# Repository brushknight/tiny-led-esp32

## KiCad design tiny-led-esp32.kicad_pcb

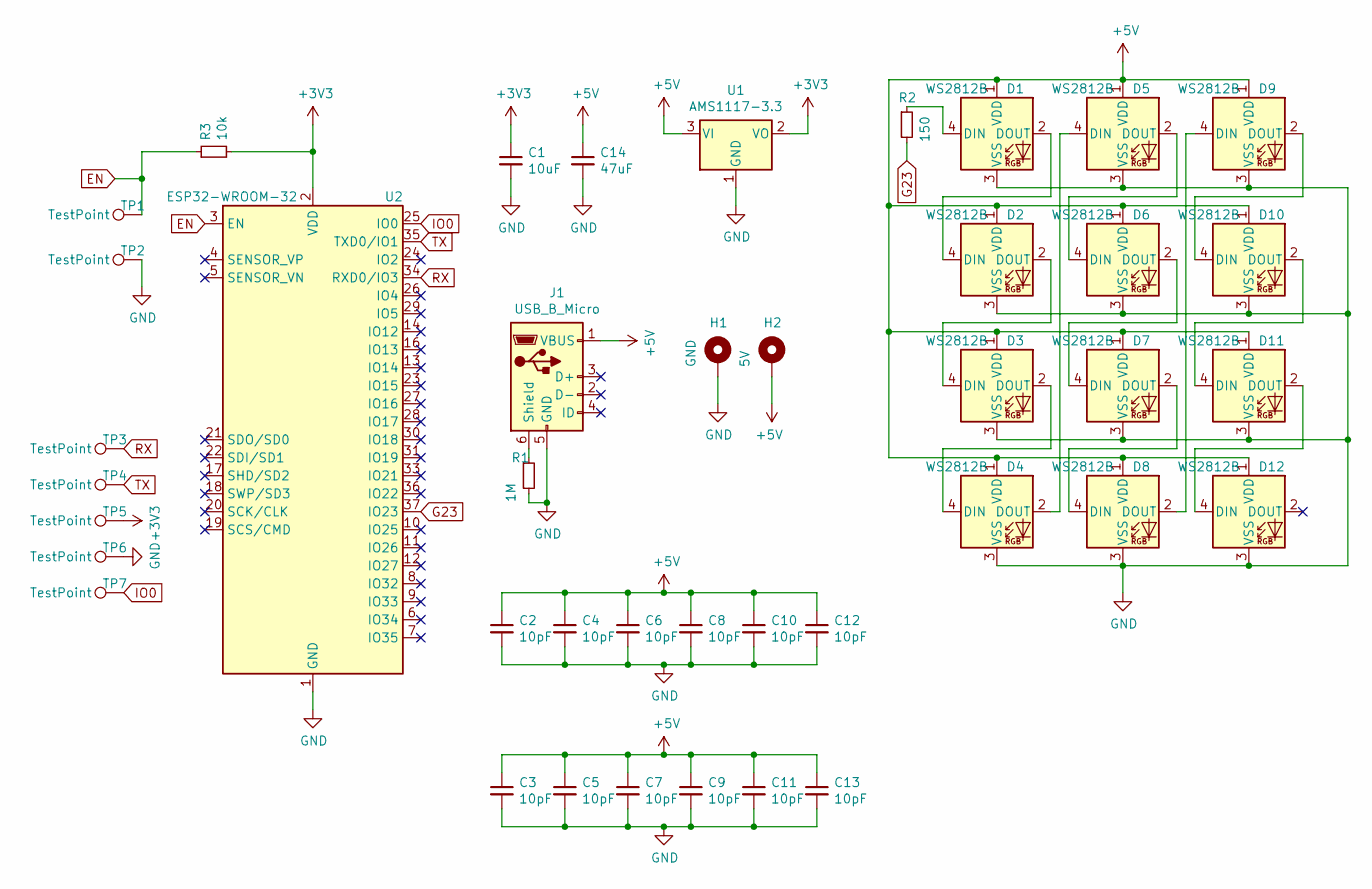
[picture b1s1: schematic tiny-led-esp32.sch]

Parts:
C1: 10uF; C_1206_3216Metric
C2, C3, C4, C5, C6, C7, C8, C9, C10, C11, C12, C13: 10pF; C_1206_3216Metric
C14: 47uF; C_1206_3216Metric
D1, D2, D3, D4, D5, D6, D7, D8, D9, D10, D11, D12: WS2812B; LED_WS2812B_PLCC4_5.0x5.0mm_P3.2mm
H1: GND; MountingHole_3.2mm_M3_Pad_Via
H2: 5V; MountingHole_3.2mm_M3_Pad_Via
J1: USB_B_Micro; USB_Micro-B_Wuerth_629105150521
R1: 1M; R_1206_3216Metric
R2: 150; R_1206_3216Metric
R3: 10k; R_1206_3216Metric
TP1, TP2, TP3, TP4, TP5, TP6, TP7: TestPoint; TestPoint_Pad_D2.5mm
U1: AMS1117-3.3; SOT-223-3_TabPin2
U2: ESP32-WROOM-32

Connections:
+3V3: C1.1, R3.2, TP5.1, U1.2 (VO), U2.2 (VDD)
+5V: C2.1, C3.1, C4.1, C5.1, C6.1, C7.1, C8.1, C9.1, C10.1, C11.1, C12.1, C13.1, C14.1, D1.1 (VDD), D2.1 (VDD), D3.1 (VDD), D4.1 (VDD), D5.1 (VDD), D6.1 (VDD), D7.1 (VDD), D8.1 (VDD), D9.1 (VDD), D10.1 (VDD), D11.1 (VDD), D12.1 (VDD), H2.1, J1.1 (VBUS), U1.3 (VI)
EN: R3.1, TP1.1, U2.3 (EN)
G23: R2.2, U2.37 (IO23)
GND: C1.2, C2.2, C3.2, C4.2, C5.2, C6.2, C7.2, C8.2, C9.2, C10.2, C11.2, C12.2, C13.2, C14.2, D1.3 (VSS), D2.3 (VSS), D3.3 (VSS), D4.3 (VSS), D5.3 (VSS), D6.3 (VSS), D7.3 (VSS), D8.3 (VSS), D9.3 (VSS), D10.3 (VSS), D11.3 (VSS), D12.3 (VSS), H1.1, J1.5 (GND), R1.2, TP2.1, TP6.1, U1.1 (GND), U2.1 (GND), U2.15 (GND), U2.38 (GND), U2.39 (GND)
IO0: TP7.1, U2.25 (IO0)
unnamed: D1.2 (DOUT), D2.4 (DIN)
unnamed: D1.4 (DIN), R2.1
unnamed: D2.2 (DOUT), D3.4 (DIN)
unnamed: D3.2 (DOUT), D4.4 (DIN)
unnamed: D4.2 (DOUT), D5.4 (DIN)
unnamed: D5.2 (DOUT), D6.4 (DIN)
unnamed: D6.2 (DOUT), D7.4 (DIN)
unnamed: D7.2 (DOUT), D8.4 (DIN)
unnamed: D8.2 (DOUT), D9.4 (DIN)
unnamed: D10.2 (DOUT), D11.4 (DIN)
unnamed: D9.2 (DOUT), D10.4 (DIN)
unnamed: D11.2 (DOUT), D12.4 (DIN)
unnamed: J1.6 (Shield), R1.1
RX: TP3.1, U2.34 (RXD0/IO3)
TX: TP4.1, U2.35 (TXD0/IO1)

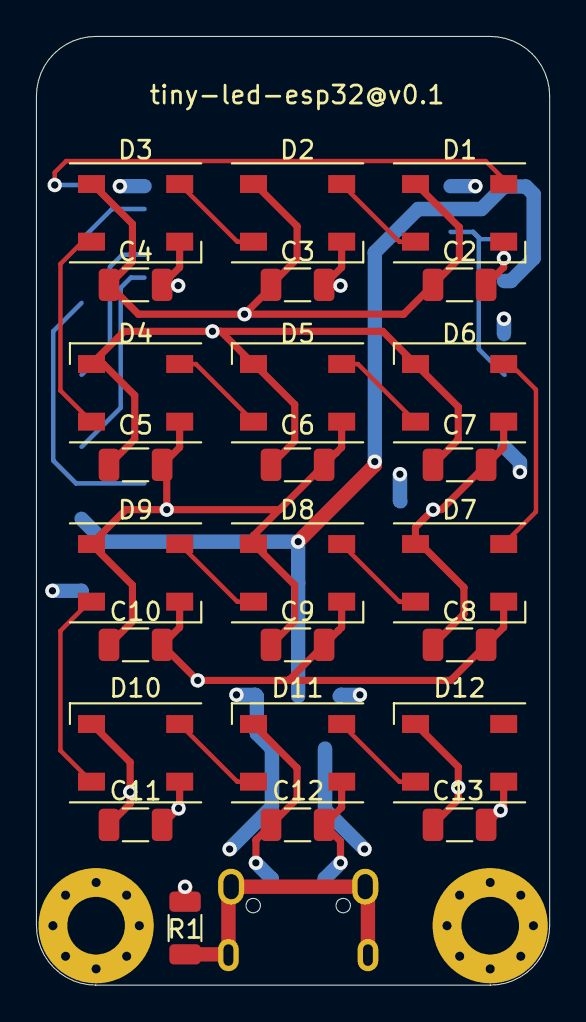
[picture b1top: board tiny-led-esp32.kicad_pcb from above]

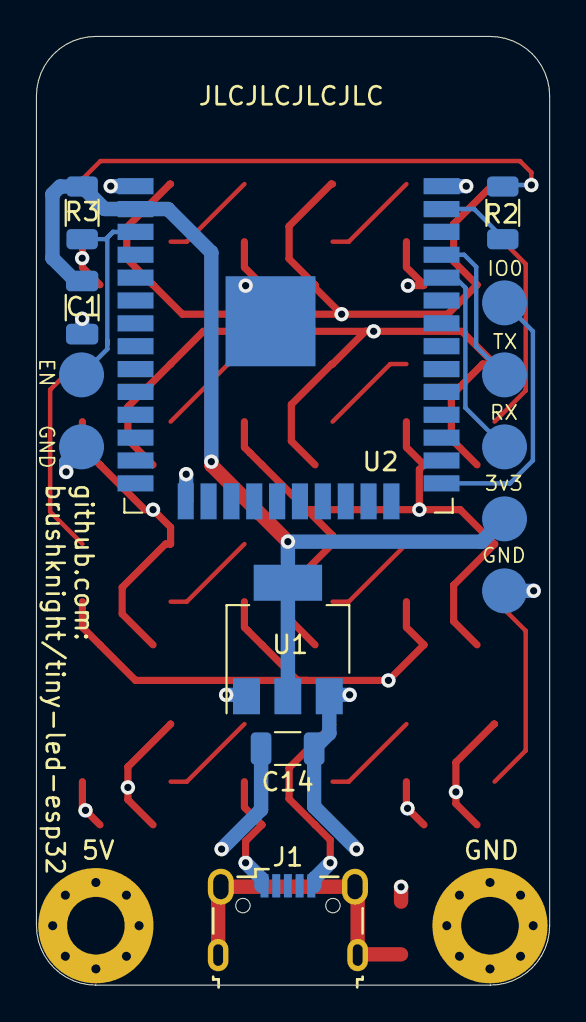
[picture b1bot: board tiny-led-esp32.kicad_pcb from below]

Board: 4 copper layers, 28.5 x 52.7 mm, 41 parts (14 on the bottom side), 21 nets.

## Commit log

2022-01-26 added mount holes, inner layers
2022-01-26 finished with v0.1
2022-07-28 dont remember
